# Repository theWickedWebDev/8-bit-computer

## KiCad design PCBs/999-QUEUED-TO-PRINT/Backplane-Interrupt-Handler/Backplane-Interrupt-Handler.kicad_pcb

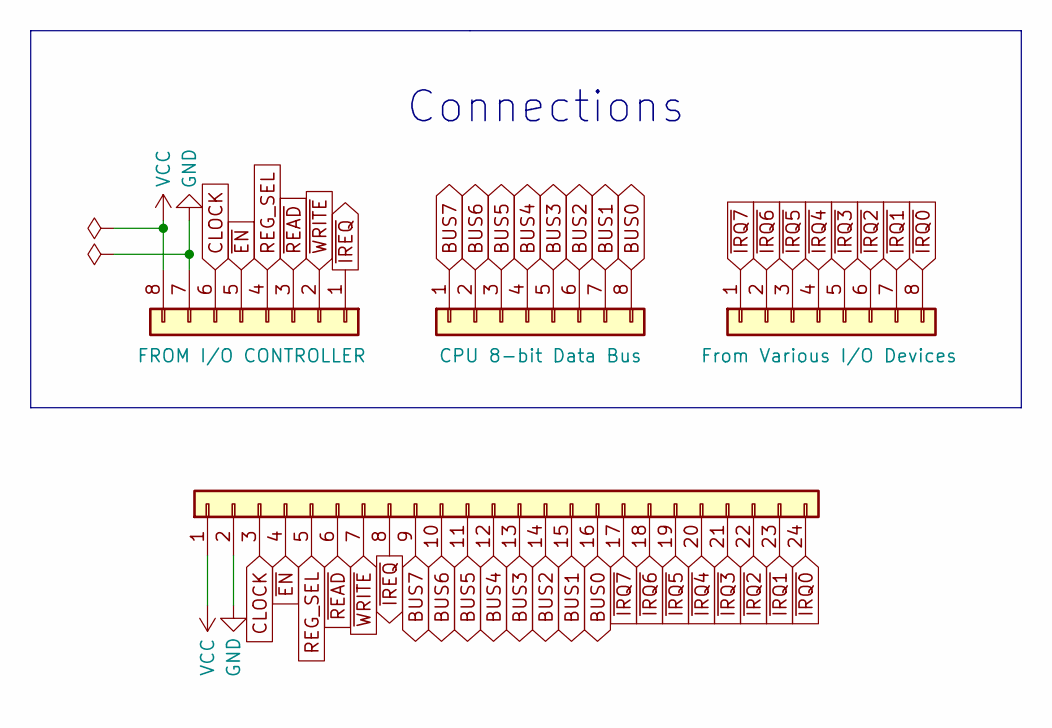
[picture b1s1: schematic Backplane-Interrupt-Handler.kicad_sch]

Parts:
J1, J3, J4: Conn_01x08; PinSocket_1x08_P2.54mm_Vertical
J2: Conn_01x24; PinSocket_1x24_P2.54mm_Horizontal

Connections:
BUS0: J2.16, J3.8
BUS1: J2.15, J3.7
BUS2: J2.14, J3.6
BUS3: J2.13, J3.5
BUS4: J2.12, J3.4
BUS5: J2.11, J3.3
BUS6: J2.10, J3.2
BUS7: J2.9, J3.1
CLOCK: J1.6, J2.3
GND: J1.7, J2.2
REG_SEL: J1.4, J2.5
VCC: J1.8, J2.1
~EN: J1.5, J2.4
~IREQ: J1.1, J2.8
~IRQ0: J2.24, J4.8
~IRQ1: J2.23, J4.7
~IRQ2: J2.22, J4.6
~IRQ3: J2.21, J4.5
~IRQ4: J2.20, J4.4
~IRQ5: J2.19, J4.3
~IRQ6: J2.18, J4.2
~IRQ7: J2.17, J4.1
~READ: J1.3, J2.6
~WRITE: J1.2, J2.7

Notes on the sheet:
Connections

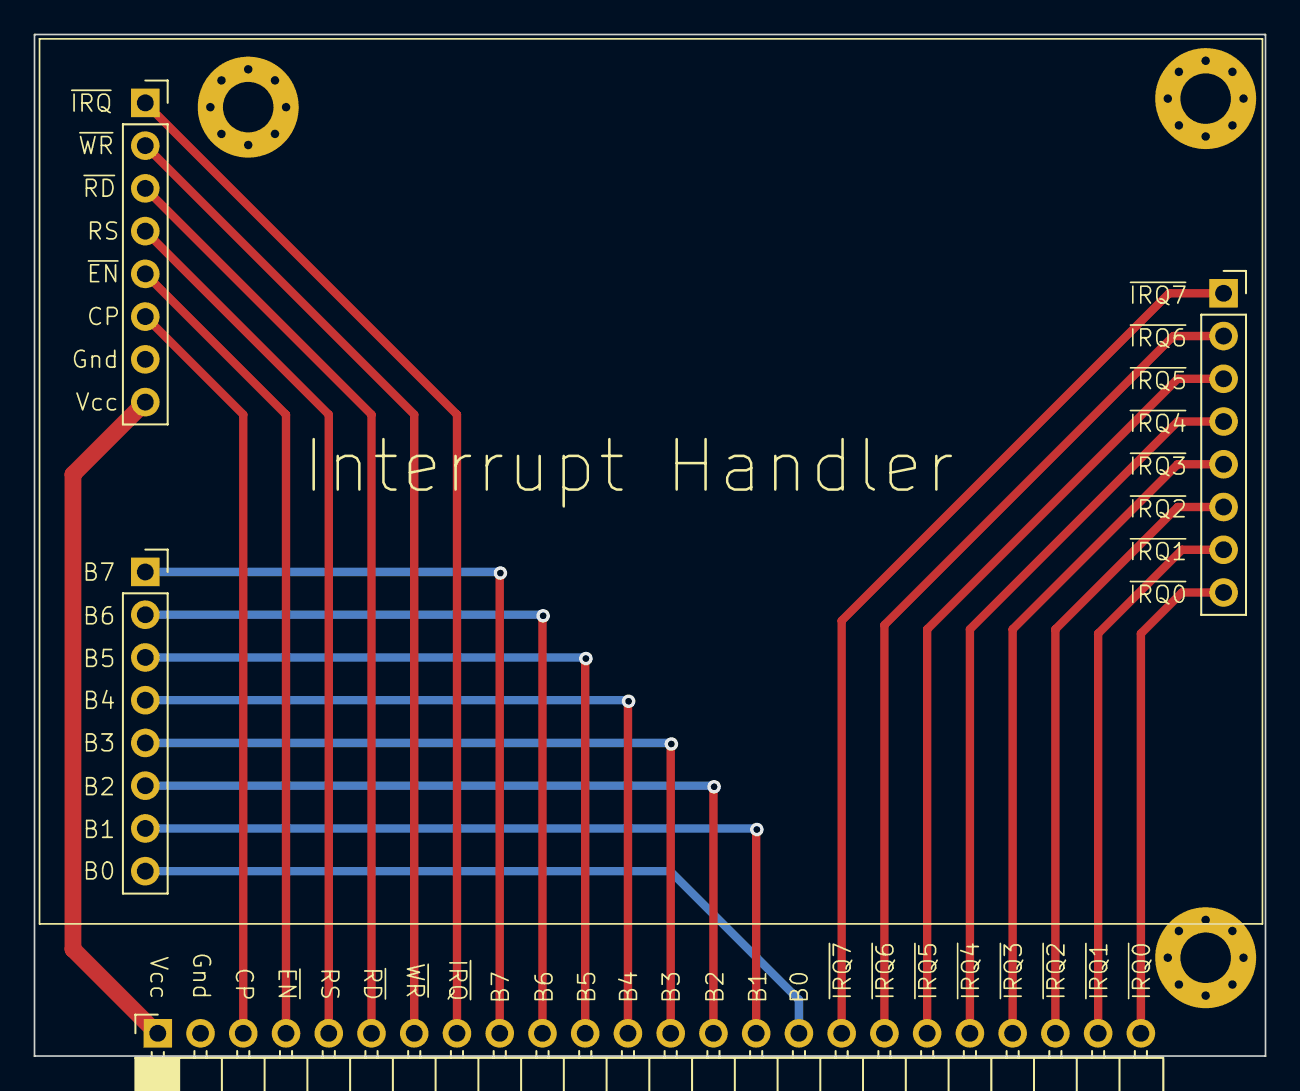
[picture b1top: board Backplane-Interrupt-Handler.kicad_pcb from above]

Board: 2 copper layers, 73.2 x 60.7 mm, 4 parts (0 on the bottom side), 24 nets.

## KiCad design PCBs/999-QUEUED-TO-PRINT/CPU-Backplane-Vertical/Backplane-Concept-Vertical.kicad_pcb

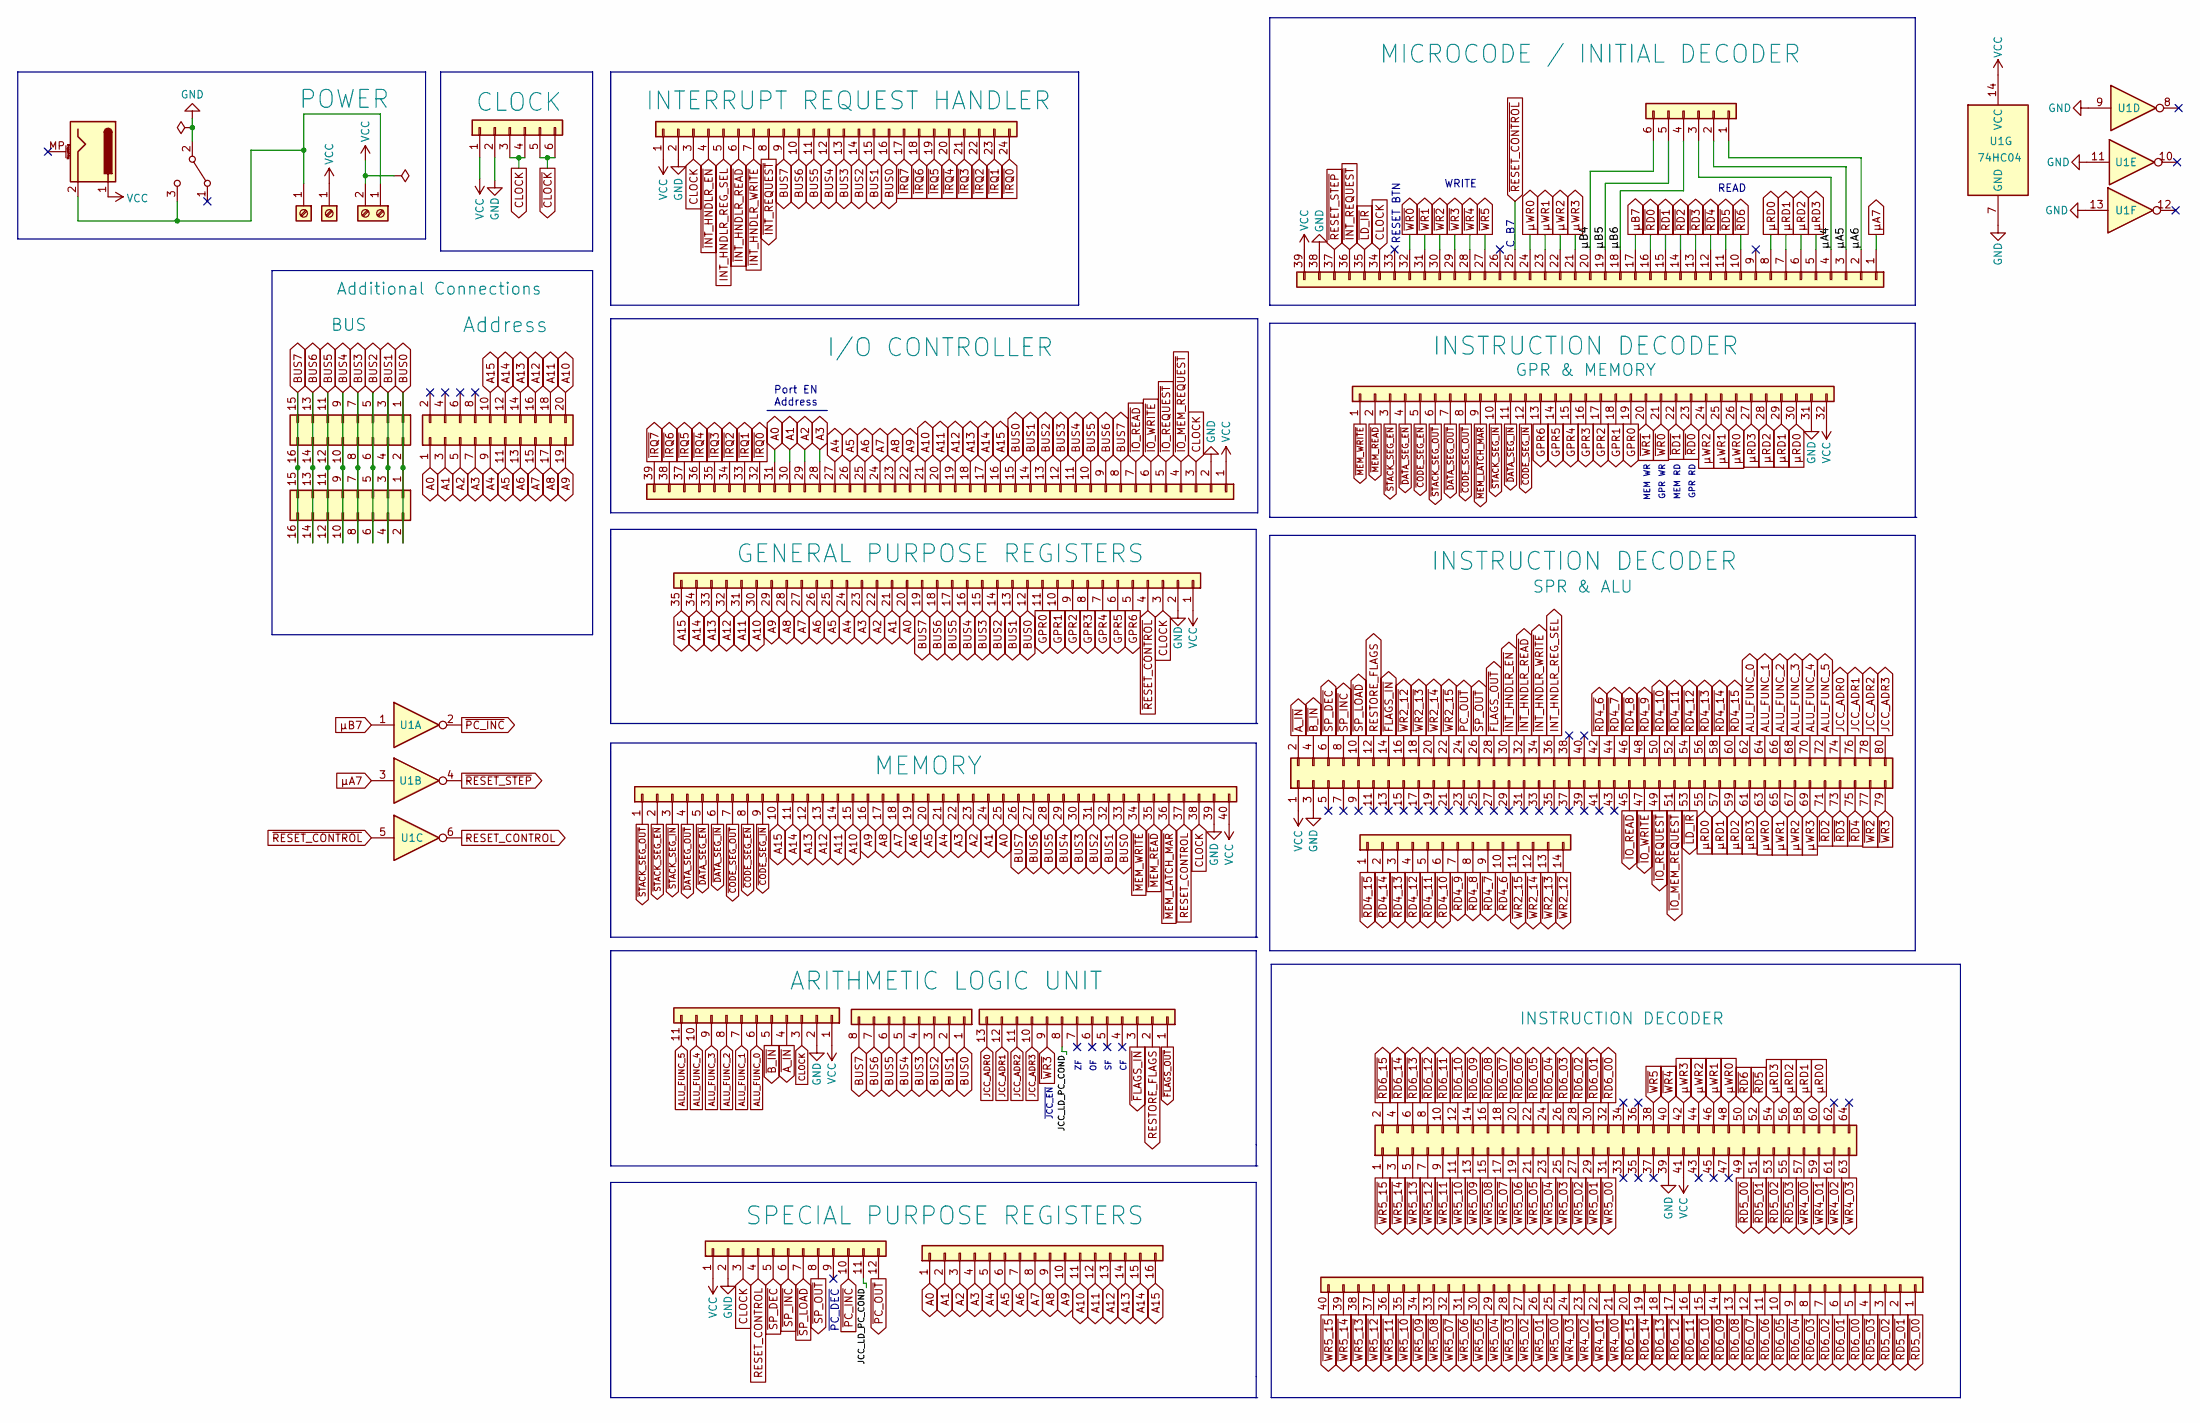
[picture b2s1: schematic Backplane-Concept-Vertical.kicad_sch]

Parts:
J1: Conn_01x12; PinSocket_2x40_P2.54mm_Vertical
J2: Conn_01x12; PinSocket_1x11_P2.54mm_Vertical
J3: Conn_01x24; PinSocket_1x12_P2.54mm_Vertical
J4: Conn_01x08; PinSocket_1x24_P2.54mm_Vertical
J5: Conn_01x40; PinSocket_1x08_P2.54mm_Vertical
J6: Conn_01x35; PinSocket_1x40_P2.54mm_Vertical
J7: Conn_01x16; PinSocket_1x35_P2.54mm_Vertical
J8: Conn_01x13; PinSocket_1x16_P2.54mm_Vertical
J9: Conn_01x06; PinSocket_1x13_P2.54mm_Vertical
J10: Screw_Terminal_01x01; PinSocket_1x06_P2.54mm_Vertical
J11, J12: Screw_Terminal_01x01; BananaJack-2mm-Single
J13: Screw_Terminal_01x02; TerminalBlock_Phoenix_MKDS-1,5-2_1x02_P5.00mm_Horizontal
J14: Conn_01x14; PinHeader_1x14_P2.54mm_Horizontal
J15: Conn_01x39; PinSocket_1x39_P2.54mm_Vertical
J16: Conn_01x39; PinSocket_1x39_P2.54mm_Horizontal
J17, J23: Conn_01x08; PinHeader_2x08_P2.54mm_Vertical
J18: Conn_01x32; PinSocket_1x32_P2.54mm_Vertical
J19: Conn_02x20_Odd_Even; IDC-Header_2x10_P2.54mm_Vertical
J20: Conn_01x06; PinHeader_1x06_P2.54mm_Horizontal
J21: Conn_01x40; PinSocket_1x40_P2.54mm_Horizontal
J22: Barrel_Jack_MountingPin; BarrelJack_Horizontal
J25: Conn_02x32_Odd_Even; PinSocket_2x32_P2.54mm_Vertical
SW1: SW_SPDT; SPDT-Slide-Switch-THT
U1: 74HC04

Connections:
/JCC_LD_PC_COND: J3.11, J9.8
/μA4: J15.4, J20.3
/μA5: J15.3, J20.2
/μA6: J15.2, J20.1
/μB4: J15.20, J20.6
/μB5: J15.19, J20.5
/μB6: J15.18, J20.4
A0: J6.25, J7.20, J8.1, J16.31, J19.1
A1: J6.24, J7.21, J8.2, J16.30, J19.3
A2: J6.23, J7.22, J8.3, J16.29, J19.5
A3: J6.22, J7.23, J8.4, J16.28, J19.7
A4: J6.21, J7.24, J8.5, J16.27, J19.9
A5: J6.20, J7.25, J8.6, J16.26, J19.11
A6: J6.19, J7.26, J8.7, J16.25, J19.13
A7: J6.18, J7.27, J8.8, J16.24, J19.15
A8: J6.17, J7.28, J8.9, J16.23, J19.17
A9: J6.16, J7.29, J8.10, J16.22, J19.19
A10: J6.15, J7.30, J8.11, J16.21, J19.20
A11: J6.14, J7.31, J8.12, J16.20, J19.18
A12: J6.13, J7.32, J8.13, J16.19, J19.16
A13: J6.12, J7.33, J8.14, J16.18, J19.14
A14: J6.11, J7.34, J8.15, J16.17, J19.12
A15: J6.10, J7.35, J8.16, J16.16, J19.10
ALU_FUNC_0: J1.62, J2.6
ALU_FUNC_1: J1.64, J2.7
ALU_FUNC_2: J1.66, J2.8
ALU_FUNC_3: J1.68, J2.9
ALU_FUNC_4: J1.70, J2.10
ALU_FUNC_5: J1.72, J2.11
BUS0: J4.16, J5.1, J6.33, J7.12, J16.15, J17.1, J17.2, J23.1, J23.2
BUS1: J4.15, J5.2, J6.32, J7.13, J16.14, J17.3, J17.4, J23.3, J23.4
BUS2: J4.14, J5.3, J6.31, J7.14, J16.13, J17.5, J17.6, J23.5, J23.6
BUS3: J4.13, J5.4, J6.30, J7.15, J16.12, J17.7, J17.8, J23.7, J23.8
BUS4: J4.12, J5.5, J6.29, J7.16, J16.11, J17.9, J17.10, J23.9, J23.10
BUS5: J4.11, J5.6, J6.28, J7.17, J16.10, J17.11, J17.12, J23.11, J23.12
BUS6: J4.10, J5.7, J6.27, J7.18, J16.9, J17.13, J17.14, J23.13, J23.14
BUS7: J4.9, J5.8, J6.26, J7.19, J16.8, J17.15, J17.16, J23.15, J23.16
CLOCK: J2.3, J3.3, J4.3, J6.38, J7.3, J10.3, J10.4, J15.34, J16.3
GND: J1.3, J2.2, J3.2, J4.2, J6.39, J7.2, J10.2, J15.38, J16.2, J18.31, J25.39, SW1.2 (B), U1.7 (GND), U1.9, U1.11, U1.13
GPR0: J7.11, J18.19
GPR1: J7.10, J18.18
GPR2: J7.9, J18.17
GPR3: J7.8, J18.16
GPR4: J7.7, J18.15
GPR5: J7.6, J18.14
GPR6: J7.5, J18.13
INT_HNDLR_REG_SEL: J1.36, J4.5
JCC_ADR0: J1.74, J9.13
JCC_ADR1: J1.76, J9.12
JCC_ADR2: J1.78, J9.11
JCC_ADR3: J1.80, J9.10
unnamed: J11.1, J13.1, J22.2, SW1.3 (C)
RESET_CONTROL: J3.4, J6.37, U1.6
RESTORE_FLAGS: J1.12, J9.2
VCC: J1.1, J2.1, J3.1, J4.1, J6.40, J7.1, J10.1, J12.1, J13.2, J15.39, J16.1, J18.32, J22.1, J25.41, U1.14 (VCC)
~A_IN: J1.2, J2.4
~B_IN: J1.4, J2.5
~CLOCK: J10.5, J10.6
~CODE_SEG_EN: J6.8, J18.5
~CODE_SEG_IN: J6.9, J18.12
~CODE_SEG_OUT: J6.7, J18.8
~DATA_SEG_EN: J6.5, J18.4
~DATA_SEG_IN: J6.6, J18.11
~DATA_SEG_OUT: J6.4, J18.7
~FLAGS_IN: J1.14, J9.3
~FLAGS_OUT: J1.28, J9.1
~INT_HNDLR_EN: J1.30, J4.4
~INT_HNDLR_READ: J1.32, J4.6
~INT_HNDLR_WRITE: J1.34, J4.7
~INT_REQUEST: J4.8, J15.36
~IO_MEM_REQUEST: J1.51, J16.4
~IO_READ: J1.45, J16.7
~IO_REQUEST: J1.49, J16.5
~IO_WRITE: J1.47, J16.6
~IRQ0: J4.24, J16.32
~IRQ1: J4.23, J16.33
~IRQ2: J4.22, J16.34
~IRQ3: J4.21, J16.35
~IRQ4: J4.20, J16.36
~IRQ5: J4.19, J16.37
~IRQ6: J4.18, J16.38
~IRQ7: J4.17, J16.39
~LD_IR: J1.53, J15.35
~MEM_LATCH_MAR: J6.36, J18.9
~MEM_READ: J6.35, J18.2
~MEM_WRITE: J6.34, J18.1
~PC_INC: J3.10, U1.2
~PC_OUT: J1.24, J3.12
~RD0: J15.16, J18.23
~RD1: J15.15, J18.22
~RD2: J1.71, J15.14
~RD3: J1.73, J15.13
~RD4_6: J1.42, J14.10
~RD4_7: J1.44, J14.9
~RD4_8: J1.46, J14.8
~RD4_9: J1.48, J14.7
~RD4_10: J1.50, J14.6
~RD4_11: J1.52, J14.5
~RD4_12: J1.54, J14.4
~RD4_13: J1.56, J14.3
~RD4_14: J1.58, J14.2
~RD4_15: J1.60, J14.1
~RD4: J1.75, J15.12
~RD5_00: J21.1, J25.49
~RD5_01: J21.2, J25.51
~RD5_02: J21.3, J25.53
~RD5_03: J21.4, J25.55
~RD5: J15.11, J25.52
~RD6_00: J21.5, J25.32
~RD6_01: J21.6, J25.30
~RD6_02: J21.7, J25.28
~RD6_03: J21.8, J25.26
~RD6_04: J21.9, J25.24
~RD6_05: J21.10, J25.22
~RD6_06: J21.11, J25.20
~RD6_07: J21.12, J25.18
~RD6_08: J21.13, J25.16
~RD6_09: J21.14, J25.14
~RD6_10: J21.15, J25.12
~RD6_11: J21.16, J25.10
~RD6_12: J21.17, J25.8
~RD6_13: J21.18, J25.6
~RD6_14: J21.19, J25.4
~RD6_15: J21.20, J25.2
~RD6: J15.10, J25.50
~RESET_CONTROL: J7.4, J15.25, U1.5
~RESET_STEP: J15.37, U1.4
~SP_DEC: J1.6, J3.5
~SP_INC: J1.8, J3.6
~SP_LOAD: J1.10, J3.7
~SP_OUT: J1.26, J3.8
~STACK_SEG_EN: J6.2, J18.3
~STACK_SEG_IN: J6.3, J18.10
~STACK_SEG_OUT: J6.1, J18.6
~WR0: J15.32, J18.21
~WR1: J15.31, J18.20
~WR2_12: J1.16, J14.14
~WR2_13: J1.18, J14.13
~WR2_14: J1.20, J14.12
~WR2_15: J1.22, J14.11
~WR2: J1.77, J15.30
~WR3: J1.79, J9.9, J15.29
~WR4_00: J21.21, J25.57
~WR4_01: J21.22, J25.59
~WR4_02: J21.23, J25.61
~WR4_03: J21.24, J25.63
~WR4: J15.28, J25.40
~WR5_00: J21.25, J25.31
~WR5_01: J21.26, J25.29
~WR5_02: J21.27, J25.27
~WR5_03: J21.28, J25.25
~WR5_04: J21.29, J25.23
~WR5_05: J21.30, J25.21
~WR5_06: J21.31, J25.19
~WR5_07: J21.32, J25.17
~WR5_08: J21.33, J25.15
~WR5_09: J21.34, J25.13
~WR5_10: J21.35, J25.11
~WR5_11: J21.36, J25.9
~WR5_12: J21.37, J25.7
~WR5_13: J21.38, J25.5
~WR5_14: J21.39, J25.3
~WR5_15: J21.40, J25.1
~WR5: J15.27, J25.38
μA7: J15.1, U1.3
μB7: J15.17, U1.1
μRD0: J1.55, J15.8, J18.30, J25.60
μRD1: J1.57, J15.7, J18.29, J25.58
μRD2: J1.59, J15.6, J18.28, J25.56
μRD3: J1.61, J15.5, J18.27, J25.54
μWR0: J1.63, J15.24, J18.26, J25.48
μWR1: J1.65, J15.23, J18.25, J25.46
μWR2: J1.67, J15.22, J18.24, J25.44
μWR3: J1.69, J15.21, J25.42

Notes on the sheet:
RESET BTN
MEM WR
Port EN Address
MEM RD
~{JCC_EN}
GPR WR
READ
~{PC_DEC}
GPR RD
C_B7
WRITE

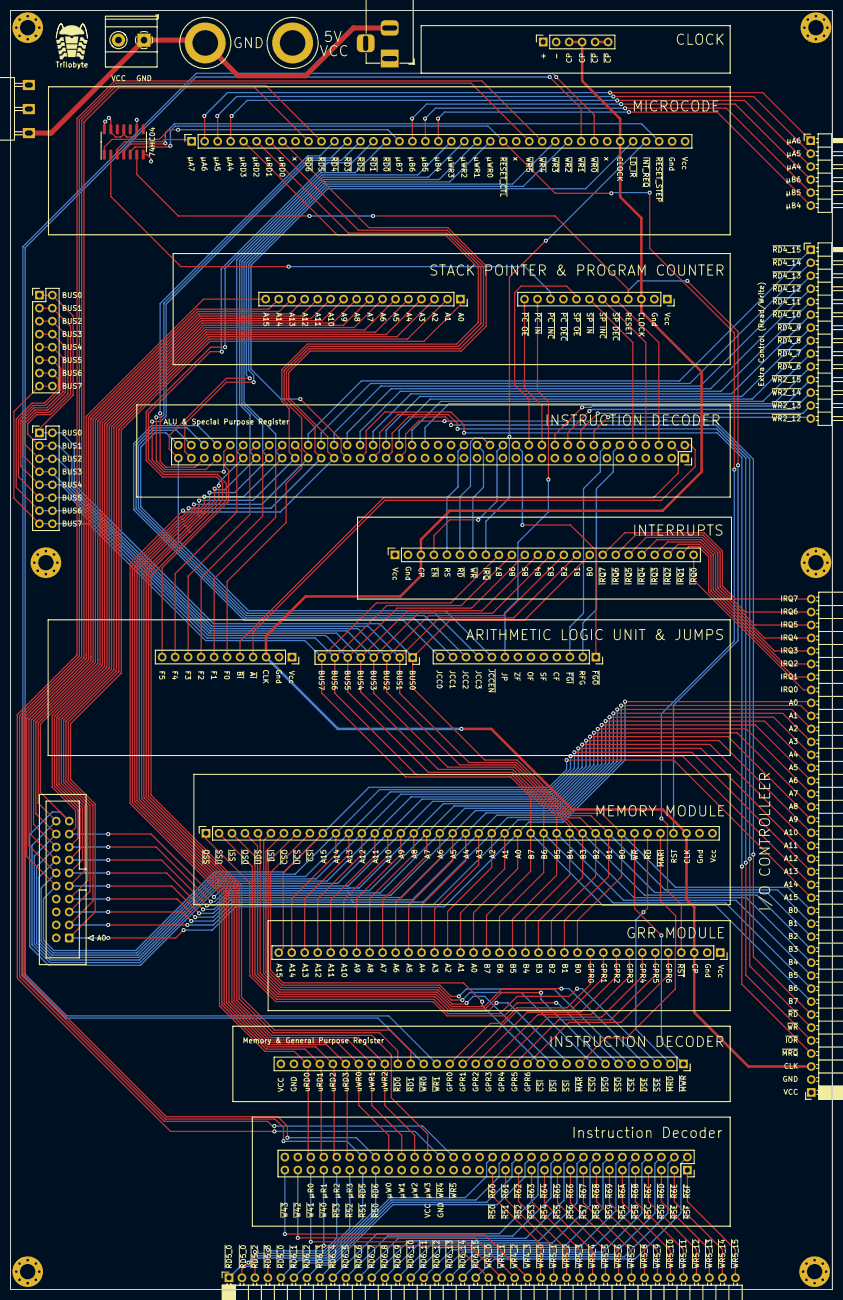
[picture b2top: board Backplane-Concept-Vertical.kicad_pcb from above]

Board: 4 copper layers, 160.8 x 250.2 mm, 26 parts (0 on the bottom side), 174 nets.

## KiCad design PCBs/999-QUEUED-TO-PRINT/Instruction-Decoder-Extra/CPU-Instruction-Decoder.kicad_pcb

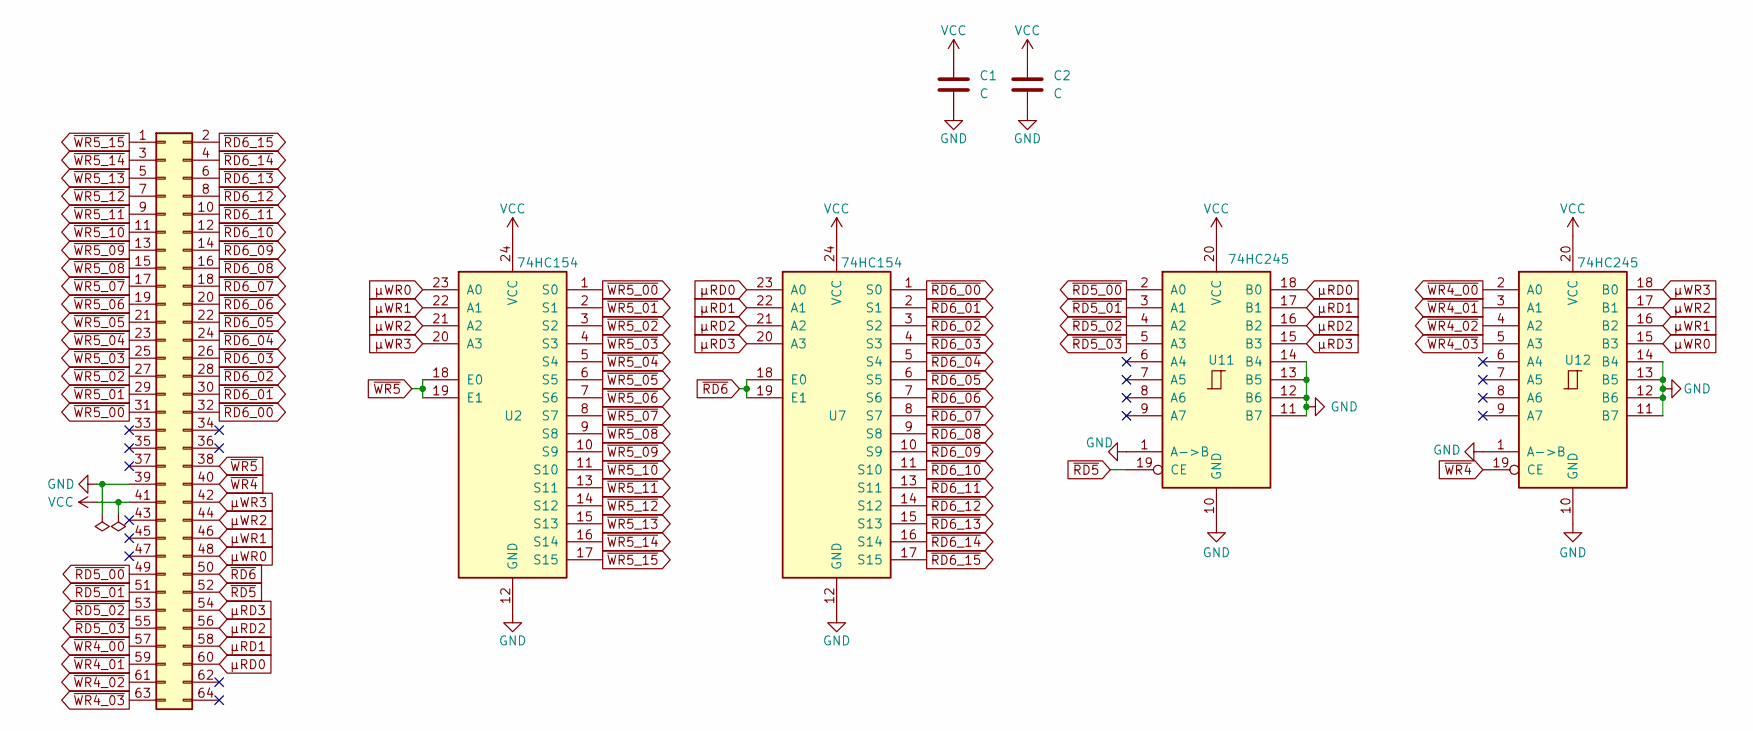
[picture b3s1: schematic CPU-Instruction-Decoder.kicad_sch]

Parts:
C1, C2: C; C_0805_2012Metric
J1: Conn_02x32_Odd_Even; PinHeader_2x32_P2.54mm_Horizontal
U2, U7: 74HC154; SOIC-24W_7.5x15.4mm_P1.27mm
U11, U12: 74HC245; SOIC-20W_7.5x12.8mm_P1.27mm

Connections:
GND: C1.2, C2.2, J1.39, U2.12 (GND), U7.12 (GND), U11.1 (A->B), U11.10 (GND), U11.11 (B7), U11.12 (B6), U11.13 (B5), U11.14 (B4), U12.1 (A->B), U12.10 (GND), U12.11 (B7), U12.12 (B6), U12.13 (B5), U12.14 (B4)
VCC: C1.1, C2.1, J1.41, U2.24 (VCC), U7.24 (VCC), U11.20 (VCC), U12.20 (VCC)
~RD5_00: J1.49, U11.2 (A0)
~RD5_01: J1.51, U11.3 (A1)
~RD5_02: J1.53, U11.4 (A2)
~RD5_03: J1.55, U11.5 (A3)
~RD5: J1.52, U11.19 (CE)
~RD6_00: J1.32, U7.1 (S0)
~RD6_01: J1.30, U7.2 (S1)
~RD6_02: J1.28, U7.3 (S2)
~RD6_03: J1.26, U7.4 (S3)
~RD6_04: J1.24, U7.5 (S4)
~RD6_05: J1.22, U7.6 (S5)
~RD6_06: J1.20, U7.7 (S6)
~RD6_07: J1.18, U7.8 (S7)
~RD6_08: J1.16, U7.9 (S8)
~RD6_09: J1.14, U7.10 (S9)
~RD6_10: J1.12, U7.11 (S10)
~RD6_11: J1.10, U7.13 (S11)
~RD6_12: J1.8, U7.14 (S12)
~RD6_13: J1.6, U7.15 (S13)
~RD6_14: J1.4, U7.16 (S14)
~RD6_15: J1.2, U7.17 (S15)
~RD6: J1.50, U7.18 (E0), U7.19 (E1)
~WR4_00: J1.57, U12.2 (A0)
~WR4_01: J1.59, U12.3 (A1)
~WR4_02: J1.61, U12.4 (A2)
~WR4_03: J1.63, U12.5 (A3)
~WR4: J1.40, U12.19 (CE)
~WR5_00: J1.31, U2.1 (S0)
~WR5_01: J1.29, U2.2 (S1)
~WR5_02: J1.27, U2.3 (S2)
~WR5_03: J1.25, U2.4 (S3)
~WR5_04: J1.23, U2.5 (S4)
~WR5_05: J1.21, U2.6 (S5)
~WR5_06: J1.19, U2.7 (S6)
~WR5_07: J1.17, U2.8 (S7)
~WR5_08: J1.15, U2.9 (S8)
~WR5_09: J1.13, U2.10 (S9)
~WR5_10: J1.11, U2.11 (S10)
~WR5_11: J1.9, U2.13 (S11)
~WR5_12: J1.7, U2.14 (S12)
~WR5_13: J1.5, U2.15 (S13)
~WR5_14: J1.3, U2.16 (S14)
~WR5_15: J1.1, U2.17 (S15)
~WR5: J1.38, U2.18 (E0), U2.19 (E1)
μRD0: J1.60, U7.23 (A0), U11.18 (B0)
μRD1: J1.58, U7.22 (A1), U11.17 (B1)
μRD2: J1.56, U7.21 (A2), U11.16 (B2)
μRD3: J1.54, U7.20 (A3), U11.15 (B3)
μWR0: J1.48, U2.23 (A0), U12.15 (B3)
μWR1: J1.46, U2.22 (A1), U12.16 (B2)
μWR2: J1.44, U2.21 (A2), U12.17 (B1)
μWR3: J1.42, U2.20 (A3), U12.18 (B0)

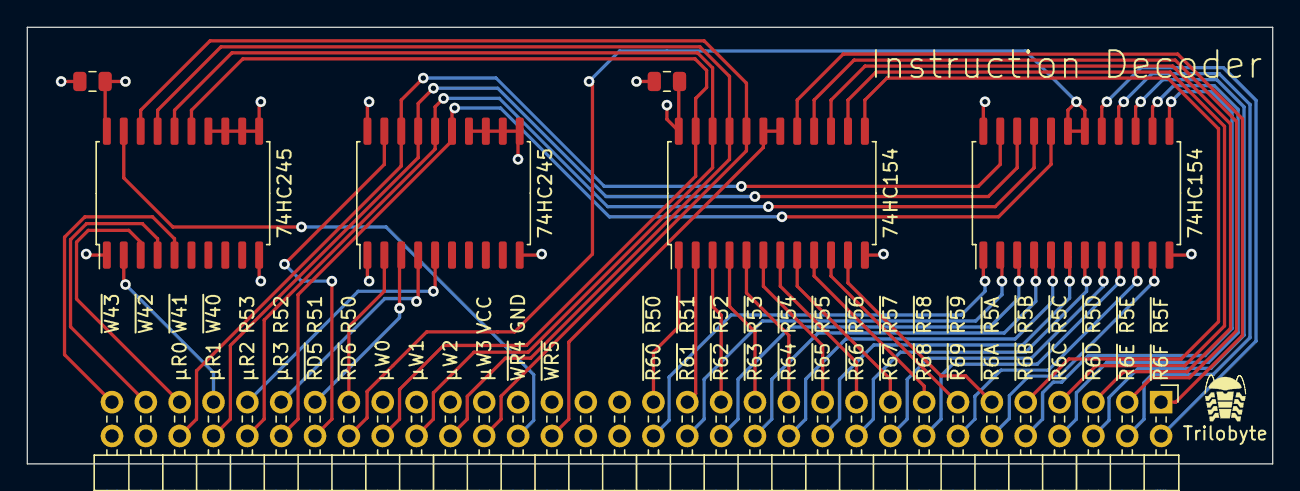
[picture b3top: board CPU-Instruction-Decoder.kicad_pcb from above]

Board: 4 copper layers, 93.5 x 32.8 mm, 7 parts (0 on the bottom side), 54 nets.

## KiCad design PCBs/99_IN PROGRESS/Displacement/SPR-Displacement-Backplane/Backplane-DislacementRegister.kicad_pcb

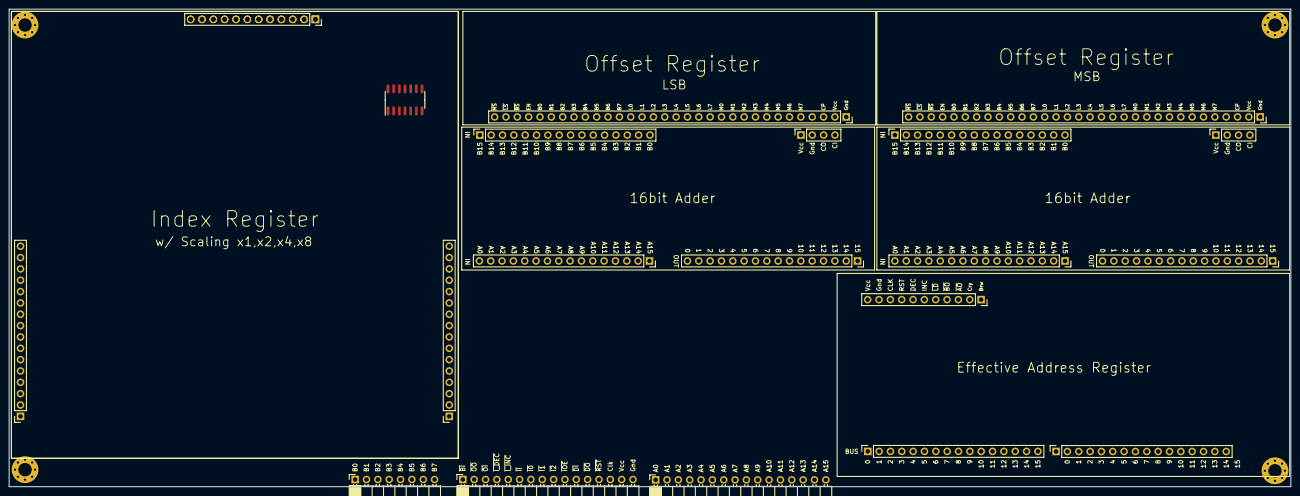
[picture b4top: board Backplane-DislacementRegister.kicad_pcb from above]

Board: 2 copper layers, 287.0 x 106.9 mm, 21 parts (1 on the bottom side), 105 nets, no tracks yet.

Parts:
J1, J4, J5, J6, J7, J8, J9, J11, J12, J16: Conn_01x16; PinSocket_1x16_P2.54mm_Vertical
J1#2: Conn_01x12; PinHeader_1x12_P2.54mm_Vertical
J2, J3: Conn_01x16; PinSocket_1x16_P2.54mm_Horizontal
J10: Conn_01x08; PinSocket_1x08_P2.54mm_Horizontal
J13, J14: Conn_01x32; PinSocket_1x32_P2.54mm_Vertical
J15: Conn_01x12; PinSocket_1x12_P2.54mm_Vertical
J17: Conn_01x11; PinSocket_1x11_P2.54mm_Vertical
J18, J19: Conn_01x06; PinSocket_1x04_P2.54mm_Vertical
U1: 74LS04; SOIC-14_3.9x8.7mm_P1.27mm

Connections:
/ADD0: J5.16, J6.16
/ADD1: J5.15, J6.15
/ADD2: J5.14, J6.14
/ADD2_0: J11.16, J12.1
/ADD2_1: J11.15, J12.2
/ADD2_2: J11.14, J12.3
/ADD2_3: J11.13, J12.4
/ADD2_4: J11.12, J12.5
/ADD2_5: J11.11, J12.6
/ADD2_6: J11.10, J12.7
/ADD2_7: J11.9, J12.8
/ADD2_8: J11.8, J12.9
/ADD2_9: J11.7, J12.10
/ADD2_10: J11.6, J12.11
/ADD2_11: J11.5, J12.12
/ADD2_12: J11.4, J12.13
/ADD2_13: J11.3, J12.14
/ADD2_14: J11.2, J12.15
/ADD2_15: J11.1, J12.16
/ADD3: J5.13, J6.13
/ADD4: J5.12, J6.12
/ADD5: J5.11, J6.11
/ADD6: J5.10, J6.10
/ADD7: J5.9, J6.9
/ADD8: J5.8, J6.8
/ADD9: J5.7, J6.7
/ADD10: J5.6, J6.6
/ADD11: J5.5, J6.5
/ADD12: J5.4, J6.4
/ADD13: J5.3, J6.3
/ADD14: J5.2, J6.2
/ADD15: J5.1, J6.1
/B0: J7.16, J9.16
/B1: J7.15, J9.15
/B2: J7.14, J9.14
/B3: J7.13, J9.13
/B4: J7.12, J9.12
/B5: J7.11, J9.11
/B6: J7.10, J9.10
/B7: J7.9, J9.9
/B8: J7.8, J9.8
/B9: J7.7, J9.7
/B10: J7.6, J9.6
/B11: J7.5, J9.5
/B12: J7.4, J9.4
/B13: J7.3, J9.3
/B14: J7.2, J9.2
/B15: J7.1, J9.1
/BUS1: J10.2, J13.27
/BUS2: J10.3, J13.26
/BUS6: J10.7, J13.22
/C0: J13.20, J16.16
/C1: J13.19, J16.15
/C2: J13.18, J16.14
/C3: J13.17, J16.13
/C4: J13.16, J16.12
/C5: J13.15, J16.11
/C6: J13.14, J16.10
/C7: J13.13, J16.9
/C8: J14.12, J16.8
/C9: J14.11, J16.7
/C10: J14.10, J16.6
/C11: J14.9, J16.5
/C12: J14.8, J16.4
/C13: J14.7, J16.3
/C14: J14.6, J16.2
/C15: J14.5, J16.1
A0: J1.16, J2.1, J4.16, J8.1
A1: J1.15, J2.2, J4.15, J8.2
A2: J1.14, J2.3, J4.14, J8.3
A3: J1.13, J2.4, J4.13, J8.4
A4: J1.12, J2.5, J4.12, J8.5
A5: J1.11, J2.6, J4.11, J8.6
A6: J1.10, J2.7, J4.10, J8.7
A7: J1.9, J2.8, J4.9, J8.8
A8: J1.8, J2.9, J4.8, J8.9
A9: J1.7, J2.10, J4.7, J8.10
A10: J1.6, J2.11, J4.6, J8.11
A11: J1.5, J2.12, J4.5, J8.12
A12: J1.4, J2.13, J4.4, J8.13
A13: J1.3, J2.14, J4.3, J8.14
A14: J1.2, J2.15, J4.2, J8.15
A15: J1.1, J2.16, J4.1, J8.16
BUS7: J10.8, J13.21, J14.21, J14.22, J14.23, J14.24, J14.25, J14.26, J14.27, J14.28
CLOCK: J3.14, J13.3, J14.3, J17.9
GND: J1#2.2, J3.16, J13.1, J14.1, J15.2, J17.10, J18.2, J19.2, U1.5, U1.7 (GND), U1.9, U1.11, U1.13
unnamed: J10.1, J13.28
unnamed: J10.4, J13.25
unnamed: J10.5, J13.24
unnamed: J10.6, J13.23
unnamed: J15.3, U1.4
OFFSET_LATCH: J13.29, J14.29, U1.2
VCC: J1#2.1, J3.15, J13.2, J14.2, J15.1, J17.11, J18.1, J19.1, U1.14 (VCC)
~DISPLACEMENT_LATCH: J3.11, J17.5
~DISPLACEMENT_OUT: J3.12, J17.3
~INDEX_C0: J1#2.7, J3.7, J15.7
~INDEX_C1: J1#2.8, J3.8, J15.8
~INDEX_C2: J1#2.9, J3.9, J15.9
~INDEX_DEC: J1#2.4, J3.4, J15.4
~INDEX_INC: J1#2.5, J3.5, J15.5
~INDEX_LOAD: J1#2.6, J3.6, J15.6
~INDEX_OE: J1#2.10, J3.10, J15.10
~OFFSET_LATCH: J3.3, U1.1
~OFFSET_OUT: J3.2, J13.31, J14.32
~RESET: J3.13, J17.8, U1.3

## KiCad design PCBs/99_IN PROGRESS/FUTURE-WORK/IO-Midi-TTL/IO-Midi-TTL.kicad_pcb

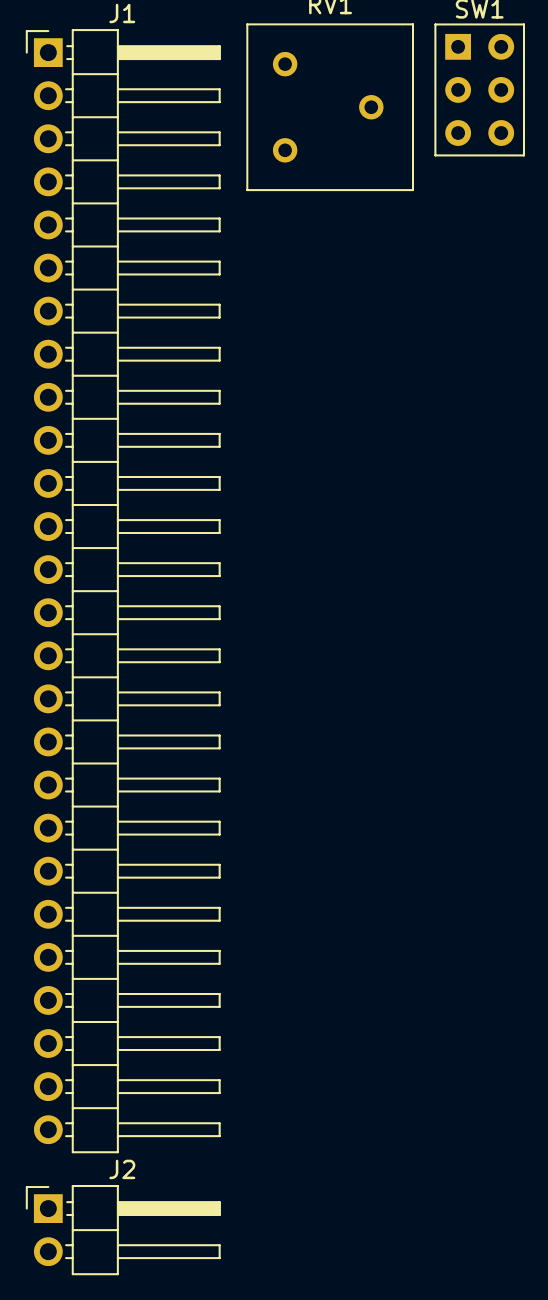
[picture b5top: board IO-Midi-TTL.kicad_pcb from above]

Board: 2 copper layers, 4 parts (0 on the bottom side), 2 nets, no tracks yet.

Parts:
J1: Conn_01x26; PinHeader_1x26_P2.54mm_Horizontal
J2: Conn_01x02; PinHeader_1x02_P2.54mm_Horizontal
RV1: R_POT_TRIM_US; Potentiometer_Bourns_3386F_Vertical
SW1: SW_Push_DPDT; SW_NKK_G1xJP

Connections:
GND: J1.25, RV1.3
SPEAKER_OUT: J2.1, J2.2

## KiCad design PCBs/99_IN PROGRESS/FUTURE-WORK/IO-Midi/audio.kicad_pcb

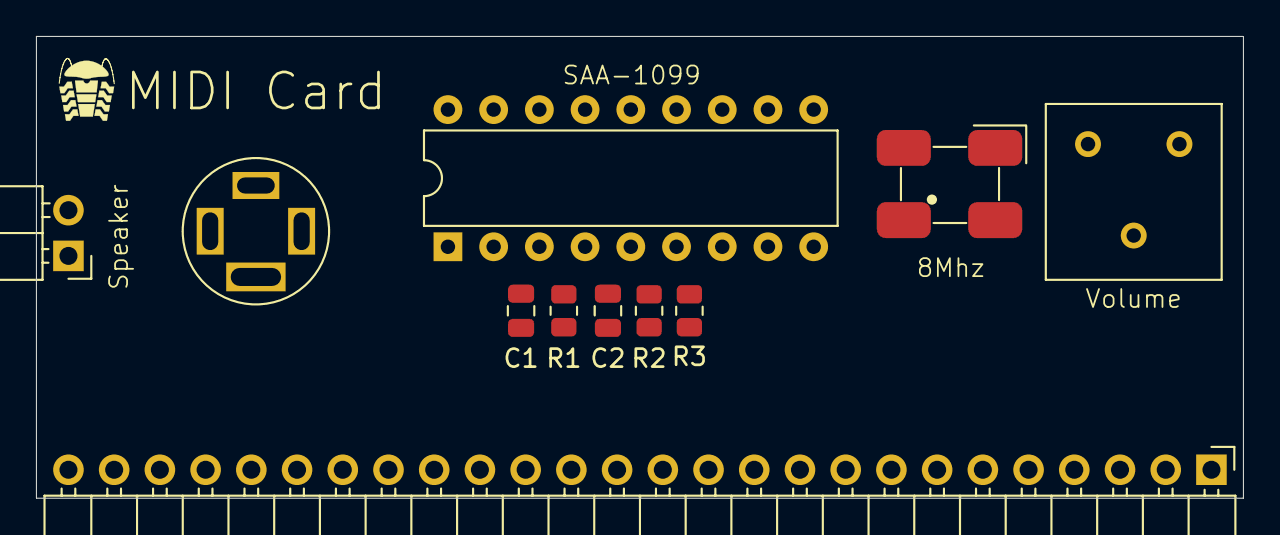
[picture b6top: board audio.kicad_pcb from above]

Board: 2 copper layers, 67.1 x 25.7 mm, 11 parts (0 on the bottom side), 18 nets, no tracks yet.

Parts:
C1, C2: C; C_0805_2012Metric
J1: Conn_01x02; PinHeader_1x02_P2.54mm_Horizontal
J2: Conn_01x26; PinHeader_1x26_P2.54mm_Horizontal
LS1: Speaker; speaker-jack
R1, R2, R3: R_Small_US; R_0805_2012Metric
RV1: R_POT_TRIM_US; Potentiometer_Bourns_3386F_Vertical
U1: SMD_Crystal; CFPS-72 SMD Clock
U2: SAA-1099; DIP-18_W7.62mm

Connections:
A4: J2.1, U2.3 (A0)
BUS0: J2.13, U2.10 (D0)
BUS1: J2.14, U2.11 (D1)
BUS2: J2.15, U2.12 (D2)
BUS3: J2.16, U2.13 (D3)
BUS4: J2.17, U2.14 (D4)
BUS5: J2.18, U2.15 (D5)
BUS6: J2.19, U2.16 (D6)
BUS7: J2.20, U2.17 (D7)
GND: C1.1, C2.1, J2.25, RV1.3, U1.2 (Gnd), U2.9 (GND)
unnamed: C1.2, R1.2, U2.4 (OUTR)
unnamed: LS1.R1, LS1.R2, RV1.2
unnamed: R3.2, U2.6 (Ref)
unnamed: U1.3, U2.8 (CLK)
SPEAKER_OUT: C2.2, J1.1, J1.2, LS1.S, LS1.T, R2.2, U2.5 (OUTL)
VCC: J2.26, R1.1, R2.1, R3.1, U1.4 (Vcc), U2.18 (VCC)
~EN: J2.24, U2.2 (~CS)
~WRITE: J2.22, U2.1 (~WR)

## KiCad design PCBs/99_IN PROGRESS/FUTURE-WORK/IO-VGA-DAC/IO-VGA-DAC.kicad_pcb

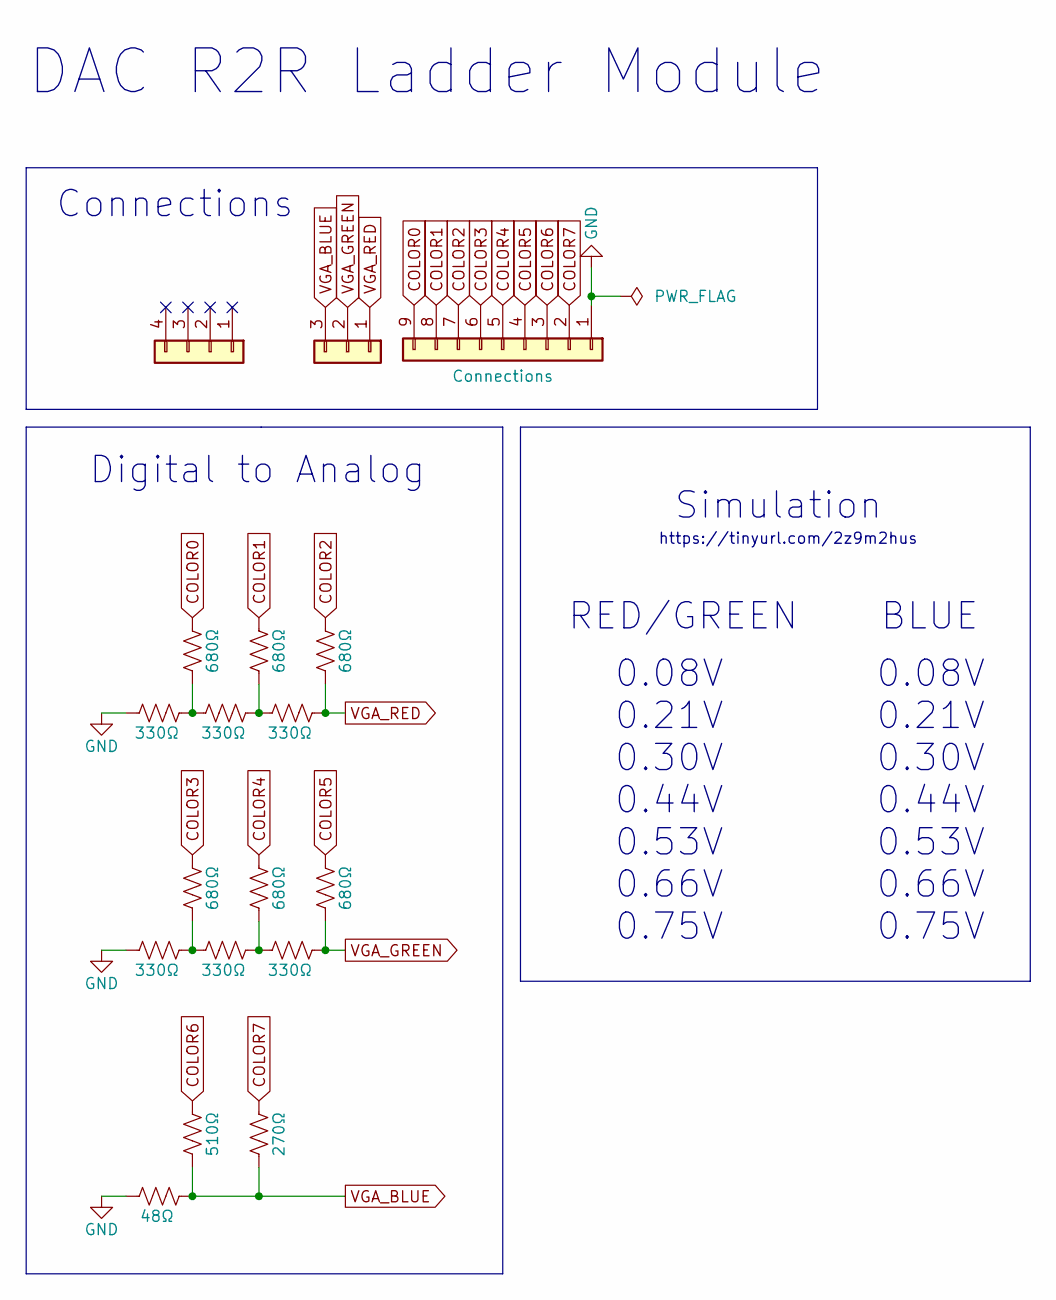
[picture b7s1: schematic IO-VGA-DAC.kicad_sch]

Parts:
J1: Conn_01x03; PinHeader_1x03_P2.54mm_Vertical
J2: Conn_01x09; PinHeader_1x09_P2.54mm_Vertical
J4: Conn_01x04; PinHeader_1x04_P2.54mm_Vertical
R1, R2, R3, R4, R5, R6, R7, R8, R10, R11, R12, R13, R14, R15, R16: R_US; R_0805_2012Metric

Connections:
COLOR0: J2.9, R4.1
COLOR1: J2.8, R10.1
COLOR2: J2.7, R15.1
COLOR3: J2.6, R5.1
COLOR4: J2.5, R11.1
COLOR5: J2.4, R16.1
COLOR6: J2.3, R6.1
COLOR7: J2.2, R12.1
GND: J2.1, R1.1, R2.1, R3.1
unnamed: R1.2, R4.2, R7.1
unnamed: R2.2, R5.2, R8.1
unnamed: R7.2, R10.2, R13.1
unnamed: R8.2, R11.2, R14.1
VGA_BLUE: J1.3, R3.2, R6.2, R12.2
VGA_GREEN: J1.2, R14.2, R16.2
VGA_RED: J1.1, R13.2, R15.2

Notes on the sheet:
0.08V 0.21V 0.30V 0.44V 0.53V 0.66V 0.75V
Simulation
BLUE
https://tinyurl.com/2z9m2hus
Digital to Analog
Connections
DAC R2R Ladder Module
RED/GREEN

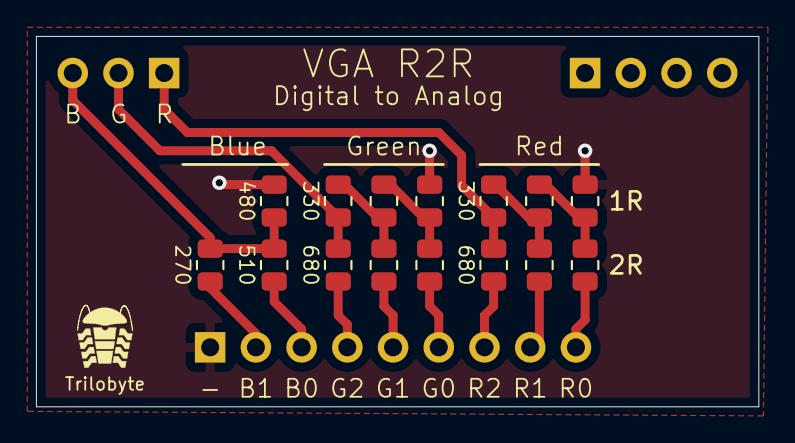
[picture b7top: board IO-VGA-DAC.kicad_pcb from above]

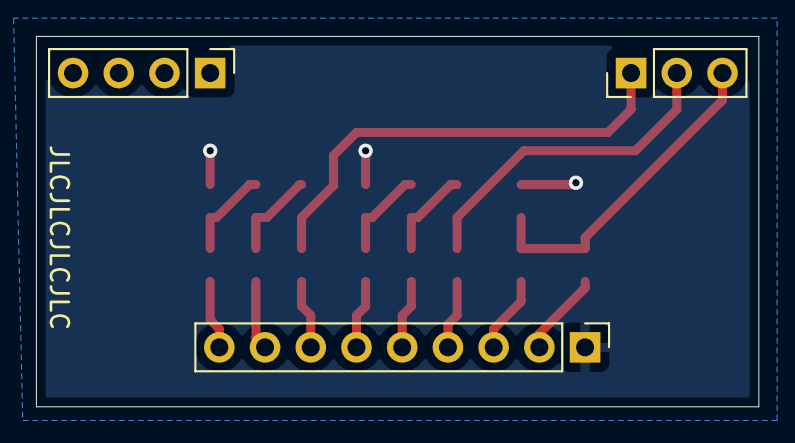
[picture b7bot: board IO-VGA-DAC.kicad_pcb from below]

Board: 2 copper layers, 40.1 x 20.6 mm, 18 parts (3 on the bottom side), 16 nets.
